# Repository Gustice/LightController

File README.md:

# LightController

A ESP32 based LED-Controller for various light scenarios.

## Purpose

This project is intended to be used as base platform for various Light projects. Its based on the ESP32 WiFi SoC and utilizes the Espressif development framework (ESP-IDF). 

On top of that this is a small hardware and board abstraction layer that simplifies the hardware access and provides further bases for device implementation.

The main purpose is of course to have fun an learn several new techniques and hacks. I also hoped to dig into a promising WiFi platform that enables a wide band of applications. As I happily discovered it was absolutely worth the time and I'm glad that I didn't stuck to arduino.

The intended Products that should result from this are extreme fancy night lights for bedrooms of my children and the stairwell and low key disco lights / ambient lights for the living room.

## Platform

This platform is capable of driving most LEDs I encountered so far (at least the very most common LEDs I have seen so far). 

- Ordinary RGB-Stripes (optionally with white channel)
- Serial LED-Stripes of both both types
  - Most common WS2812 (with RTZ-protocol)
  - Less common APA102 (with easy to use SPI)
- I2C-Expander for single or chains of LEDs

The main board integrates two switches, two analogue inputs and 1 encoder to be integrated in controlling of the station. It also can utilize a UART interface to other protocol bridges or a infrared interface which are also both prepared (the IR-Interface would come at cost of one digital function).

The board also aims to drive short LED-strips solidly with 5 V power supply. Hence it integrates also a small boost-converter.

The next picture shows a block diagram of the platform. Note that the expander board is not designed yet and the main-board will be eventually redesigned to be smaller an perhaps also provide a battery management circuitry.

The next picture shows the first Device I build up. It is solidly for implementation purpose.

The next picture shows a web GUI page to control the LED colors. It currently only supports to control exactly the first LED of each channel.

## Usage

There is currently not very much useful stuff going on. But to get faster familiar with this project this could help you to read. 

The device is flashed in three steps. One can use the VS-Tasks defined in the Firmware-Project for it:
 - `Flash & Monitor`: Builds and flashes the app to target. Note that certain config files will be remain missing until also the parameter partition and webserver partition is also flashed.
 - `Flash Data-Image`: Flashes the config files on the parameter partition (therefor the folder *factoryCfg* is packed to binary and flashed)
 - `Flash Web-Image`: Flashes the files for the webserver to the server partition (therefor the folder *serverPages* is backed to binary and flashed)

After powerup the device provides a WiFi-access point. 

- SSID `cLight`
- Password `FiatLux!`

You can connect to the device and display the root page by typing e.g. "192.168.4.1/" (at least in my case). On this page you see some (currently) little relevant in formation and can navigate to set up your WiFi-parameter or to setup the Lights.

- If you setup the WiFi-parameter the next time the device will try to connect to the provided station. You can Reset the parameter by pressing button 1 at start up 
- If you setup the LEDs you currently can only setup the first LED-slave.

## Development

The development is done in *Visual Studio Code* so far. To be able to join the development you must have the [IDF](https://docs.espressif.com/projects/esp-idf/en/latest/esp32/get-started/index.html) installed. Add also the path to the installed *IDF* as system path variable.

**Note**: This project is based on the idf version `ESP-IDF v4.2-dev-1034-ge599b794b`. I missed the step to stick to a certain tag or something. Sorry for that. You pretty sure will have to make minor adaptions on things like Queues or Wifi parameter.

However, to be able to compile the code you must start vs code from command line with exported environment variables

- Open console in your project path
- Type `%IDF_PATH%\export.bat` to setup the environment for used toolchain
- Type `code .` to open current path in *VS Code* 
- No you are able to start build-process by just hitting `Ctrl+Shift+B`

To be able to flash your ESP you need a USB to UART bridge, that also exposes RTS and DTR pins. These are needed to reset and set the ESP32 into programming mode.

## Architecture
- The main applications instantiates the driver and starts the web server. 
- Each component is in charge of an more or less well defined part of the whole structure
    - Filesystem reads the files from data-storage and partly interprets them
    - LightEffect is in charge of conduction the soft switching of the lights and provides all color definitions
    - MyConnect is a component to establish wifi connection by either providing a network in Access-Point mode or connection to an Access-Point.
    - MyWeb provides the http-server and the Rest-API
    - MyHal is a composite of simple c++ modules to simplify the usage of the SoC hardware
    - Devices utilizes MyHal to drive different devices connected to the main board
- The flash is divided in 3 main partitions. 
    - Program flash
    - Data-storage
    - Web-storage
- The web-server is build in a way similar to a single-page-application manner, but not that strictly. Most content is intended to be generated dynamically on page. The data is intended to be set or fetched via rest-requests.
- Device-IDs and device configuration are read from data-storage. The http-webserver, provides the
    whole webpage from web-storage. 

**Note**: Many of the components are partly ore even mostly tested by unit-tests (that are run locally on the computer not on the SoC). Currently catch2 is used as test-framework.

**Note**: You can also use the ServerMock.py script to emulate parts of the behavior of the http-webserver. At least display and the navigation across the websites. Also partly demo data is already generated.

## Issues

This project is anything but finished. I have several open tasks and they somehow appear to increase rather than getting less. 

- Status LEDs don't display any status yet (just fancy blink codes).
- Linear power states with configurable current flow are not designed yet.
- Wide parts are written more in c-style rather than c++. Sorry i was a little in hurry

## ToDos

- OverTheAirUpdates would be nice
- Design for linear Endstage (expander board)
- Adaption of ZigBee
- Logging should be switched to network path. Means some network placed destination must be configured as logging destination.

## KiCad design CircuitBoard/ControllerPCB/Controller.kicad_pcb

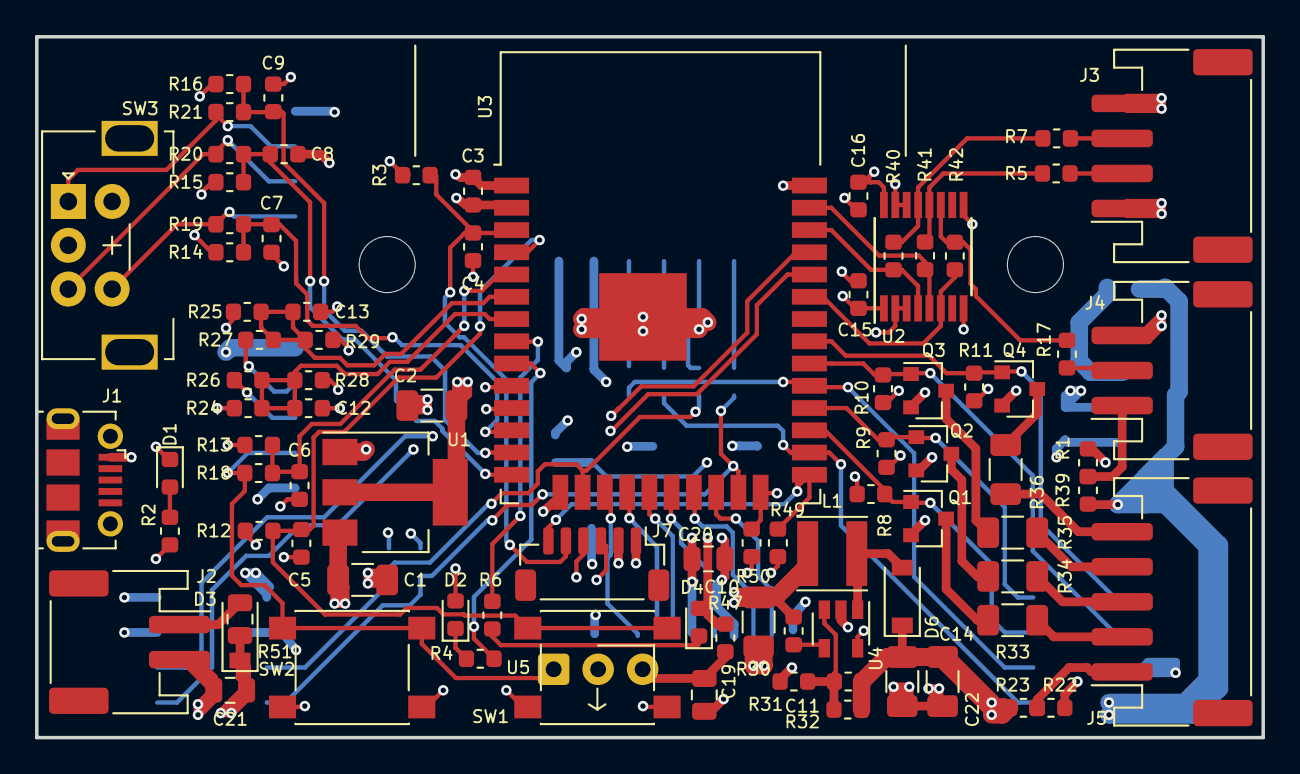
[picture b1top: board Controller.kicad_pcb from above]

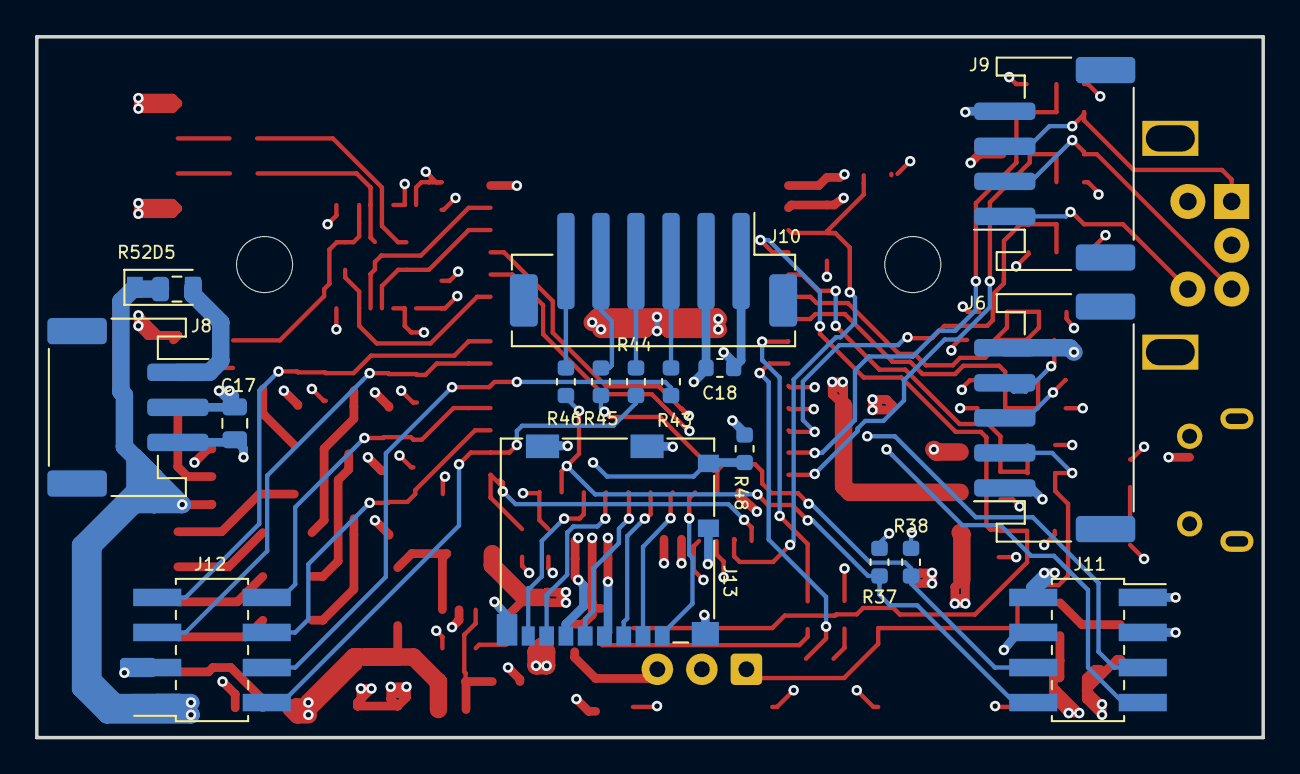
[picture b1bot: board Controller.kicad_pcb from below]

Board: 4 copper layers, 70.0 x 40.0 mm, 106 parts (18 on the bottom side), 72 nets.

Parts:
C1, C2, C10: 10uF; C_1206_3216Metric
C3, C4, C5, C6, C7, C8, C9, C12, C13, C15, C16, C18: 100nF; C_0603_1608Metric
C11: 56pF; C_0603_1608Metric
C14, C22: 4,7uF; C_1206_3216Metric
C17, C19, C20, C21: 1uF; C_0805_2012Metric
D1: green; LED_0603_1608Metric
D2: red; LED_0603_1608Metric
D3, D5, D6: SS24FL; D_SOD-123
D4: blue; LED_0603_1608Metric
J1: USB_B_Micro; USB_Micro-B_Molex-105017-0001
J2: PH-S2B; JST_PH_S2B-PH-SM4-TB_1x02-1MP_P2.00mm_Horizontal
J3, J9: PH-S4B; JST_PH_S4B-PH-SM4-TB_1x04-1MP_P2.00mm_Horizontal
J4, J8: PH-S3B; JST_PH_S3B-PH-SM4-TB_1x03-1MP_P2.00mm_Horizontal
J5, J6: PH-S5B; JST_PH_S5B-PH-SM4-TB_1x05-1MP_P2.00mm_Horizontal
J7: SH-BM6; JST_SH_BM06B-SRSS-TB_1x06-1MP_P1.00mm_Vertical
J10: PH-S6B; JST_PH_B6B-PH-SM4-TB_1x06-1MP_P2.00mm_Vertical
J11, J12: 2x4 2mm; PinSocket_2x04_P2.00mm_Vertical_SMD
J13: Micro_SD_Card_Det; microSD_HC_Molex_104031-0811
L1: 10 uH; L_Taiyo-Yuden_MD-4040
Q1, Q2, Q3, Q4: IRLML2030; SOT-23
R1, R5, R7, R17, R22, R23, R39: 0R; R_0603_1608Metric
R2: 2.2k; R_0603_1608Metric
R3, R8, R9, R10, R11, R12, R13, R14, R15, R16, R28, R29, R30, R31, R37, R38, R48, R49, R50: 10k; R_0603_1608Metric
R4, R6: 470R; R_0603_1608Metric
R18, R19, R20, R21, R26, R27, R43, R44, R45, R46, R47: 100R; R_0603_1608Metric
R24, R25, R40, R41, R42: NC; R_0603_1608Metric
R32: 86k; R_0603_1608Metric
R33, R34, R35, R36: 0R; R_1206_3216Metric
R51, R52: NC; R_0805_2012Metric
SW1, SW2: SW_SPST; SW_Push_1P1T_NO_6x6mm_H9.5mm
SW3: EN12-VS11AF18; RotaryEncoder_EN12-VS11AF18
U1: AP1117-33; SOT-223-3_TabPin2
U2: 74AXP4T245; TSSOP-16_4.4x5mm_P0.65mm
U3: ESP32-WROOM-32
U4: LMR62421XMF; SOT-23-5
U5: TSDP341xx; Vishay_MOLD-3Pin

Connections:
+3V3: C2.1, C3.1, C15.2, C18.1, C20.1, D2.2, D4.2, J6.1, J7.1, J10.1, J11.2, J13.4, R3.1, R12.1, R13.1, R14.1, R15.1, R16.1, R24.1, R25.1, R37.2, R38.2, R47.2, R48.2, R49.1, U1.2, U2.1, U2.2, U2.3, U3.2
+5V: C1.1, C10.1, C16.1, C17.1, C21.1, D3.1, J1.1, J3.1, J8.2, J11.1, L1.1, R1.2, R2.1, R22.2, R30.1, R51.1, U1.3, U2.16, U4.5
+12P: C11.1, C14.1, C22.1, D5.1, D6.1, J12.1, R23.2, R32.2, R39.1, R52.2
/ADO: R42.2, U2.6, U3.33
/AI1: C13.1, R25.2, R27.2, R29.1, U3.6
/AI2: C12.1, R24.2, R26.2, R28.1, U3.7
/Blue: J12.5, Q3.1, R10.1, U3.30
/Clk: J13.5, U3.20
/Cmd: J13.3, U3.19
/DI1: C5.1, R12.2, SW1.2, U3.4
/DI2: C6.1, R13.2, R18.2, U3.5
/Dac1: J11.7, U3.10
/Dac2: J11.5, U3.11
/Data0: J13.7, U3.21
/Data1: J13.8, U3.22
/Data2: J13.1, U3.17
/Data3: J13.2, U3.18
/Detect: J13.10, R48.1, R50.2, U3.24
/EN: C4.1, J7.5, R3.2, U3.3
/EncA: C9.1, R16.2, R21.2, U3.13
/EncB: C8.1, R15.2, R20.2, U3.14
/EncSw: C7.1, R14.2, R19.2, U3.12
/Ext1: J12.4, R43.1, U3.29
/Ext2: J12.2, R44.1, U3.26
/Green: J12.8, Q2.1, R9.1, U3.28
/IO0: J7.6, R49.2, U3.25
/RXD: J7.3, U3.34
/Red: J12.6, Q1.1, R8.1, U3.27
/SCL: J11.8, R37.1, R46.1, U3.23
/SCLK: R40.2, U2.4, U3.36
/SDA: J11.6, R38.1, R45.1, U3.16
/SDO: R41.2, U2.5, U3.37
/StatB: R6.1, U3.8
/StatR: R4.1, U3.9
/TXD: J7.4, U3.35
/White: J12.7, Q4.1, R11.1, U3.31
/pDI2: J6.2, R18.1, SW2.2, U5.1
/pEA: J9.3, R21.1, SW3.A
/pEB: J9.2, R20.1, SW3.B
/pESw: J9.1, R19.1, SW3.S1
GNDD: C1.2, C2.2, C3.2, C4.2, C5.2, C6.2, C7.2, C8.2, C9.2, C10.2, C12.2, C13.2, C14.2, C15.1, C16.2, C17.2, C18.2, C19.2, C20.2, C21.2, C22.2, D1.1, J1.5, J1.6, J2.2, J3.4, J4.3, J6.5, J7.2, J8.3, J9.4, J10.2, J11.3, J11.4, J12.3, J13.6, J13.9, J13.11, Q1.2, Q2.2, Q3.2, Q4.2, R8.2, R9.2, R10.2, R11.2, R28.2, R29.2, R31.2, R50.1, SW1.1, SW2.1, SW3.C, SW3.S2, U1.1, U2.8, U2.9, U2.14, U2.15, U3.1, U3.15, U3.38, U3.39, U4.2, U5.2
unnamed: C11.2, R31.1, R32.1, U4.3
unnamed: C19.1, R47.1, U5.3
unnamed: D1.2, R2.2
unnamed: D2.1, R4.2
unnamed: D3.2, J2.1, R51.2
unnamed: D4.1, R6.2
unnamed: D5.2, J8.1, R52.1
unnamed: D6.2, L1.2, U4.1
unnamed: J3.2, R5.1
unnamed: J3.3, R7.1
unnamed: J4.1, R1.1, R39.2
unnamed: J4.2, R17.1
unnamed: J5.1, R22.1, R23.1
unnamed: J5.2, R33.1
unnamed: J5.3, R34.1
unnamed: J5.4, R35.1
unnamed: J5.5, R36.1
unnamed: J6.3, R26.1
unnamed: J6.4, R27.1
unnamed: J10.3, R43.2
unnamed: J10.4, R44.2
unnamed: J10.5, R45.2
unnamed: J10.6, R46.2
unnamed: Q1.3, R33.2
unnamed: Q2.3, R34.2
unnamed: Q3.3, R35.2
unnamed: Q4.3, R36.2
unnamed: R17.2, R42.1, U2.11
unnamed: R30.2, U4.4
unnamed: R7.2, R40.1, U2.13
unnamed: R5.2, R41.1, U2.12

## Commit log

2020-10-26 feature: Main-part of firmware added
2020-10-26 feature: Connectivity-parts added
2020-10-26 feature: Wifi-connect added
2020-10-26 feature: HAL added
2020-10-26 feature: Devices Added
2020-10-26 feature: LightEffect-Machine added
2020-10-26 proj: Project configuration added
2020-10-26 tests: Unit-Tests added
2020-10-26 doc: Documentation parts added
2020-10-26 doc: Simulation of first schematic parts added
2020-10-26 board: Board design added
2020-10-27 doc: Some documentation for initial publishment
2020-10-27 proj: Clang-Format file added
2020-12-08 fix: Small fixes on test-project
2020-12-08 tests: Refactor of tests and different project setup
2020-12-08 doc: Additional hints in readme
2020-12-10 fix: Test again rely on prebuild
2021-01-31 feature: Spiffs test with simple file read
2021-02-01 feature: successfully migrating webpages to Spiffs-Partiotion
2021-02-03 refactor: Changing function signature based on example
2021-02-03 refactor: Welcome-Page style seriously overworked
2021-02-03 feature: Preparing of dynamically build Setup form
2021-02-03 feature: Prepare of Debug-View
2021-02-04 feature: Gui is now fully autogenerated
2021-02-04 feature: Messages implemented
2021-02-05 refactor: Routes changed to constants. Also first Test with requesting DeviceConfig
2021-02-08 tests: Preparing of unit tests
2021-02-08 tests: unit-Test project for web API now functional
2021-02-08 refactor: Tidy up web api for better testability
2021-02-08 feature: Callback for Reading current data-set
2021-02-08 fix: Problem with termination of file-String
2021-02-10 feature: Request and welcome page changed to async ... also interpretation of responses implemented
2021-02-10 tests: Tried to debug simulated app
2021-02-11 feature: Get requests implemented and tested with local host
2021-02-11 proj: Circuit board opend with new version
2021-02-11 feature: Sending and Requesting tested. Paths are not fully finished though
2021-02-16 refactor: tidy up webpages - page and app oriented pairwise
2021-02-16 tests: Tests with web-module are compiling now (linker errors still present)
2021-02-18 tests: Unit-Tests for Web-Project almost working
2021-02-22 feature: ApplyTo-Parsing implemented ... Tests are finally running now (with compiler warnings though)
2021-02-23 tests: Tests of processor functions and several optimisations to make tests work
2021-02-24 tests: Getter implemented and tested
2021-02-24 function: Modified behavior in case of no defined apply string
2021-02-26 featrue: Getter also evaluate applyTo string
2021-02-26 doc: New Picture
2021-02-26 tests: Preparing FileSystemTests
2021-02-27 tests: Parsing config in progress
2021-02-28 function: implementing Device-Config interpretation
2021-03-01 feature: Device-Driver accumulates all color operations
2021-03-01 tests: refactoring of main tested
2021-03-01 feature: more sophisticated parsing of spans in apply2-String
2021-03-02 fix: minor bugfixes on Driver module
2021-03-02 fix: Small fix in interpretation of span apply strings
2021-03-02 fix: messed up with color assignment of rgb strip and WS-Strip
2021-03-02 tests: New test-approach of server-Pages implemented
2021-03-02 feature: Getter finally implemented
2021-03-03 fetaure: Get-Requests implemented ... almost everything is working now
2021-03-04 proj: Tidy up a little and minor improvements
2021-03-04 proj: Clickable links from problem matcher ... finally!!
2021-03-04 refactor: Device-Driver refactored
2021-03-04 doc: readme finished
2021-03-06 feature: Status-LED added
2021-03-26 Feature: LightEffect replaced with latest version
2021-03-26 feature: Schemata for Config-Files created
2021-03-26 reafactor: Color:color_t changed to Color_t for practival reasons
2021-04-13 function: Interpretation of start-color-configuration with delay from JSON
2021-05-17 feature: Additional routes and GUI for configuration management
2021-05-17 feature: Light-Effect put into order
2021-05-21 feature: New routes and tests prepared
2021-05-25 refactor: GrayValueMsg and ColorMsg delegates concentrated to one
2021-05-25 refactor: additional configuration fields to control EffectProcessor
2021-05-27 function: Controlling of channel effects (in generic implementation) prepared
2021-05-27 refactor: Parser functions exported to separate file
2021-05-28 test: Start Image tested with effect-processors
2021-05-31 function: Reading of effect channels implemented
2021-05-31 function: Download of Setups implemented
2021-06-02 refactor: optimization of DeviceDriver regarding resting. Also documentation added
2021-06-02 doc: documentation and formatting
2021-06-02 tests: Further testing and debugging of DeviceDriver
2021-06-02 function: GetRequests to generic interface implemented and tested
2021-06-02 refactor: Modification in generic GetRequest Callback
2021-06-03 fix: Debugging of image processing and loading
2021-06-03 doc. Updates in readme
